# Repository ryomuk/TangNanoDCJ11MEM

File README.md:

# TangNanoDCJ11MEM
Memory system and UART implemented on Tang Nano 20K for DEC DCJ11 PDP-11 Processor

This document is written mostly in Japanese. If necessary, please use a translation service such as DeepL (I recommend this) or Google.

- 本プロジェクトはTang Console 138Kを用いた続編[TangConsoleDCJ11MEM](https://github.com/ryomuk/TangConsoleDCJ11MEM)があります．
- このREADMEおよび[hdl.old](./hdl.old)フォルダ配下のREADMEに書かれている不安定である旨の記述は2024年に作成したrev1.1基板のものです．rev.2.2になってかなり安定しましたが，記録として残しておきます．

# 概要
- PDP-11の命令セットを持つCPU「DEC DCJ11」のメモリシステムとUARTをFPGA(TangNano20K)上に実装する試みです．信号のインターフェース部分に[tangNano-5V](https://github.com/ryomuk/tangnano-5V)を使用しています．(rev.3.1基板では不要)
- FPGAに実装するのはメモリやUARTなどの周辺回路部分だけで，CPU自体は本物を使用します．ソフトウェアやFPGAによるシミュレータやエミュレータではなく，本物のCPUを動かします．
- "TangNanoDCJ11"だとTangNano上にDCJ11を実装したみたいな名前になってしまうので，"MEM"を付けて"TangNanoDCJ11MEM"という名前になっています．
- まずベアメタルで動かしたところ安定して動きました．
- 次に，PC-11(Paper-Tape Reader/Punch)エミュレータでPaper-Tape BASICをロードして実行することができました．
- さらに，UNIX first edition (UNIX V1)を動かすために，ディスク(RF11, RK11)や外部演算装置(KE11)のエミュレータを実装したところ，それなりに動くようになりました．

# 最近の話題
- 2025/09/03: 本プロジェクトの続編[TangConsoleDCJ11MEM](https://github.com/ryomuk/TangConsoleDCJ11MEM)を公開
- 2025/09/05: rev2.2基板公開
- 2025/09/22: レベル変換ICを搭載した基板rev3.1を公開
- 2025/09/29: RT-11 v4用のHDLを公開
- 最新版は下記の通り
  - レベル変換外付け版([rev2.2](pcb/rev2.2))．(別途[TangNano5V](https://github.com/ryomuk/tangnano-5V)が必要です．)
  - レベル変換搭載版([rev3.1](pcb/rev3.1))
  - 上記のどちらもHDLコードは共通です．
    - [UNIX用のHDLコード](./hdl/unix)(unix-v1, unix-v6 共通)
    - [tapebasic用のHDLコード](./hdl/tapebasic)
    - [RT11v4用のHDLコード](./hdl/rt11v4)

# 主なファイル一覧
```
.
├── diskimage : SDメモリ用データ
│   ├── Caldera-license.pdf : UNIXのライセンス条項
│   ├── sd-unix-v1.dsk      : unix v1用disk image
│   └── sd-unix-v6.dsk      : unix v6用disk image
├── hdl              : rev2.2, rev3.1基板用HDLコード
│   ├── rt11v4
│   ├── tapebasic
│   └── unix
├── hdl.old          : rev1.1基板用HDLコード
│   ├── baremetal
│   ├── tapebasic
│   ├── unix-v1
│   └── unix-v6
├── pcb
│   ├── rev1.1      : rev1.1基板
│   ├── rev2.2      : rev2.2基板
│   └── rev3.1      : rev3.1基板
└── README.md        : このファイル
```
- diskimageフォルダ内にあるSDメモリ用のイメージファイルはUNIXのオリジナルソースからの派生物なので，ライセンス条件は Caldera-license.pdf (昔のBSD?)に従います．
- その他の部分についてはMITライセンスです．

## Gowin FPGA Designerの設定について
- implフォルダをgitから除外したら設定ファイルも除外されてしまったのでコンパイル時にエラーが出るかもしれません．Configuration->Dual-Purpose Pin で"Use SSPI as regular IO"をチェックし下さい．

# 基板のバージョンについて
- [TangConsole138Kを用いたプロジェクト](https://github.com/ryomuk/TangConsoleDCJ11MEM)を開始した際に，CLK2に同期させるとかなり安定するという知見が得られたので，アップデートするついでに各種パッチを反映させた基板(rev2.2)を作成しました．
- ついでに，レベル変換を搭載した基板(rev3.1)も作成しました．
- それぞれの基板は下記のような関係にあります．
```
rev1.1
↓ unix v1, v6用パターンカット，ジャンパ, HALTのダイオード追加, CLK2同期化
rev2.2
↓ レベル変換(TangNano5V相当)を基板上に搭載(CPUの入力信号(FPGA→CPU)については省略)
rev3.1
```
- rev1.1基板に「unix-v1, v6用のパターンカット，ジャンパ線」，「CLK2とGPIO_RXを33Ωで接続」，「HALTのダイオード」を追加することでrev2.2基板と同じ回路になり，rev2.2基板用のHDLコードで動作します．
- rev3.1基板はrev2.2基板にレベル変換を搭載しただけなので同じHDLコードが動きます．
- rev1.1基板用のHDLコードはrev2.2, rev3.1基板では動きません．

# ハードウェア
## FPGAに実装した機能
- Initialization Sequence時のPower-Up Configuration Register設定
- メモリ 32K×16bit
- UART．TangNanoのUSB経由およびGPIO経由の2系統．シリアルの設定は基本的には115200bps,8N1Nにしています．(UNIX V6だと7N1Nにしないと文字化けする現象あり．)
- BS0, BS1は見ていません．TangNano20Kではピンが足りなかったのと，DAL[15:0]とAIO[3:0]を見ればとりあえず十分だったので．
- DAL[21:16]も見ていません．
- PC-11(Paper-Tape Reader/Punch)エミュレータを実装しました．(Paper tape BASICを実行する用で，UNIXでは動きません．)
- ディスクドライブ(RF11, RK11)，外部演算装置(KE11-A)，クロック(KW11-L)等，UNIX V1の動作に必要な装置のエミュレータを実装しました．

## rev3.1基板 (PCB rev3.1)
- レベル変換ICを基板上に実装しました．これによりTang Nano 20KをTangNano5Vを使わずに直接搭載できます．
- ピンアサインはrev2.2基板と同じなので，FPGA用のコードはrev2.2用のものを使用します．
- WS2812のアレイを接続するための端子を用意しました．
- レベル変換ICのOE_nをdisableにしてCPUとTangNanoを切り離すためのジャンパ端子を用意しました．(初めて搭載するときなど，FPGAに別の回路が書かれているようなとき用．)

#### BOM (PCB rev3.1)
|Reference          |Qty| Value          |Size |Memo |
|-------------------|---|----------------|-----|-----|
|C1,C2|2|68pF|||
|C3,C4, C5, C6|4|0.1uF|||
|C7,C8|2|0.33uF|||
|C9    |1|47uF|||
|D1    |1|1N4148|||
|J1    |1|IC socket |40pin DIP 800mil|TangNano20K用．幅800milなので1x20のpin socketを2列実装．|
|J2,J3|2  |pin header or socket|1x30|任意．テストや観測，実験用．|
|J4                 |1  |pin header      |1x02|任意．OE_nをdisableにする用|
|J5                 |1  |pin socket      |1x04 L字|WS2812アレイ用|
|J6                 |1  |pin header      |1x06 L字|UART用|
|LED1    |1||||
|R1 |1|1M|||
|R2 |1|33|||
|R3,R4,R5,R6,R7,R8,R9,R10,R11,R12,R13,R14,R15|13|10k|
|R16|1|100k  || 値はLEDに合わせて任意．|
|SW1,SW2  |2  |tactile SW      |6mmxH4.3mm|例: https://akizukidenshi.com/catalog/g/g103647/ |
|U1                 |1  |DCJ11           |60pin DIP 1300mil| 1x30 の丸ピンソケット2列|
|U2,U3,U4,U5  |4  |SN74CB3T3245DWR(又は DW) | SOIC-20| パッケージサイズに注意|

|Y1                 |1  |18MHz           |HC49|例: https://mou.sr/3WcWExh , 周波数を変えられるようにソケットの使用をお勧めします．|

- SN74CB3T3245はパッケージサイズに注意．SOIC-20はDWかDWRです．PWやPWRではありません．
- R2は"33k"ではなく"33"です．ダンピング抵抗なので．
- R12，最近のLEDは明るいので100kぐらいでちょうど良かったりします．使うLEDに応じて適切な値を選んで下さい．

## rev2.2基板 (PCB rev2.2)
- rev1.1基板でunixを動かすために必要だったパターンカットとジャンパ配線を反映させました．
- CLK2をGPIO_RXだったピンに入力して，回路をCPUのクロックと同期させました．
- 上記に伴い，基板のUART端子はデバッグログ用のTXだけになりました．
- 電源供給をTangNanoからだけにしてDCジャックを廃止しました．
- HALTスイッチのところの抵抗をダイオードに変更しました．
- unix(v1, v6)を動作させるためのプロジェクトは[hdl/unix](hdl/unix/)を使用して下さい．
- SDメモリ用のイメージファイルは[./diskimage](./diskimage)にあるものがそのまま使えます．

#### BOM (PCB rev2.2)
|Reference          |Qty| Value          |Size |Memo |
|-------------------|---|----------------|-----|-----|
|C1, C2|2|68pF|||
|C3, C4|2|0.33uF|||
|C5    |1|47uF|||
|D1    |1|1N4148|||
|J1    |1|IC socket |40pin DIP 600mil|TangNano5V用．1x20のpin socket 2列でも可．|
|J2,J3 |2|pin header or socket|1x20|任意．テストや観測，実験用．|
|J4,J5 |2  |pin header or socket|1x30|任意．テストや観測，実験用．|
|J6                 |1  |pin header      |1x06 L字|UART用|
|LED1    |1||||
|R1 |1|1M|||
|R2 |1|33|||
|R3,R4,R5,R6,R7,R8,R9,R10,R11,R12,R13,R14|12|10k|
|R15|1|100k  || 値はLEDに合わせて任意．|
|SW1,SW2  |2  |tactile SW      |6mmxH4.3mm|例: https://akizukidenshi.com/catalog/g/g103647/ |
|U1                 |1  |DCJ11           |60pin DIP 1300mil| 1x30 の丸ピンソケット2列|
|Y1                 |1  |18MHz           |HC49|例: https://mou.sr/3WcWExh , 周波数を変えられるようにソケットの使用をお勧めします．|

## rev1.1基板 (PCB rev1.1)
- rev1.0はいくつか修正箇所があったので修正しました．
- CPUが白いので基板も白くしてみました．
- CPUおよびTangNanoの電源をどこから供給するかを2箇所のジャンパで切り替えられるようにしました．詳細は回路図と基板上のシルクを見て下さい．
- プルダウン抵抗(R2〜R6)を100kから10kに変更しました．(rev1.1a)
- UNIXを動かすにはJP1のパターンのカット，数本のジャンパ配線が必要です．詳細は[UNIX V1](hdl.old/unix-v1/)参照．

#### BOM (PCB rev1.1)
|Reference          |Qty| Value          |Size |Memo |
|-------------------|---|----------------|-----|-----|
|C1,C2              |2	|0.33uF	         ||DECのプロセッサボードで0.33uFを使っていたので．0.1uFでもいいかもしれない．|
|C3                 |1  |47uF            |||
|C4,C5              |2  |68pF            |||
|D1                 |1  |LED             || |
|J1                 |1  |DC Jack         ||例: https://akizukidenshi.com/catalog/g/g106568/ |
|J2                 |1  |pin header      |1x02|DC Jackからの5VをTangNanoに供給するとき用．(そのときはTangNanoのUSBは外すこと)．|
|J3                 |1  |pin header      |1x03|CPUへの5VをDC JackからにするかUSB(TangNano)からにするかの選択用．|
|J4                 |1  |IC socket       |40pin DIP 600mil|TangNano5V用．1x20のpin socket 2列でも可．|
|J5,J6              |2  |pin header or socket|1x20|任意．テストや観測，実験用．|
|J7                 |1  |pin header      |1x06 L字|UART用|
|J8,J9              |2  |pin header or socket|1x30|任意．テストや観測，実験用．|
|JP1                |   |                ||任意．sctl_nとcont_nを切断したときにpin headerを立てる用．実装する場合は先にパターンをカットして下さい．(unix-v1では切断して使います)|
|R1                 |1  |100k            || 値はLEDに合わせて任意．|
|R2～R6             |5 |10k            || プルダウン用．入力電流がmax10μAなので大きめでいいかと思ったら意外にノイズが大きいので100kから10kに変更しました．|
|R7～R16             |10 |100k            || プルアップ用．10k〜100kぐらいで任意．|
|R17                |1  |1M              |||
|SW1                |1  |toggle SW       ||例: https://akizukidenshi.com/catalog/g/g100300/ |
|SW2,SW3            |2  |tactile SW      |6mmxH4.3mm|例: https://akizukidenshi.com/catalog/g/g103647/ |
|U1                 |1  |DCJ11           |60pin DIP 1300mil| 1x30 の丸ピンソケット2列|
|Y1                 |1  |18MHz           |HC49|例: https://mou.sr/3WcWExh , 低速(2MHzで確認済み,もっと遅くても動きそう)でも動きます．周波数を変えられるようにソケットの使用をお勧めします．|

# [応用例(hdl.old/)](hdl.old/)
## [ベアメタル(hdl.old/baremetal)](hdl.old/baremetal/)
- クロス環境で作成したプログラムを実行します．
- HDLは小規模なので，いろいろ試すベースラインに最適です．

## [tape basic(hdl.old/tapebasic)](hdl.old/tapebasic/)
- 二次記憶をエミュレートするために手始めに作った習作です．
- PC11(tape reader/pucnch)エミュレータで，tape BASICを読み込んで起動します．
- SDメモリを使う練習用に作ったものなのでとりあえず動きます程度のものです．
- PDP11GUIに，console ODT経由でpaper tape softwareをロードする機能があるようなので，いろいろなpaper tape softwareを試すという目的であればベアメタルでPDP11GUIを使うことをお勧めします．

## [UNIX V1(hdl.old/unix-v1)](hdl.old/unix-v1/)
- SDメモリを使ったdiskエミュレータを作成し，UNIX V1を動かしてみました．
- 最初はかなり不安定でしたが，だいぶ安定して動くようになってきました．

## [UNIX V6(hdl.old/unix-v6)](hdl.old/unix-v6/)(実験用)
- unix-v1用をベースにUNIX V6に必要な機能を逐次追加中です．修正のたびにV1の動作確認をするのは面倒なのでV1用と分けることにしました．

# 動画
- [PDP-11 Paper-Tape BASIC running on DCJ-11 Processor](https://www.youtube.com/watch?v=F_eFMz5ysK8)

- [UNIX V1 on DEC DCJ-11 with TangNano 20K (under development)](https://www.youtube.com/watch?v=DT7xJWeF46Y)

- [UNIX V1 on DEC DCJ-11 with TangNano 20K](https://www.youtube.com/watch?v=G9AFgAaTexo)

# 旧版
## ブレッドボード版
- console ODT(Octal Debug Technique)の動作確認をするところから始めて，[豊四季タイニーBASIC](https://github.com/vintagechips/ttbasic_arduino)を軽微な修正で動かせるところまで確認しました．
- クロックは18MHzで動きました．遅い方は2MHzでも動きました．

## PCB版 rev1.0
最初に作った基板です．とりあえず動きました．

# 関連情報
## データシート等
### bitsavers
- [DCJ11 Microprocessor User's Guide](http://www.bitsavers.org/pdf/dec/pdp11/1173/EK-DCJ11-UG-PRE_J11ug_Oct83.pdf), DEC, EK-DCJ11-UG-PRE(Preliminary)
- [Index of /pdf/dec/pdp11/j11](http://bitsavers.trailing-edge.com/pdf/dec/pdp11/j11/)
- [Index of /pdf/dec/pdp11/1173](http://bitsavers.trailing-edge.com/pdf/dec/pdp11/1173/)

## 先行事例，先駆者たち
- [PDP-11/HACK](http://madrona.ca/e/pdp11hack/index.html), Brent Hilpert
- [My PDP-11 Projects](https://www.5volts.ch/pages/pdp11hack/), Peter Schranz
- [PDP11 on a breadboard A.K.A. J11 Hack](https://www.chronworks.com/J11/), Len Bayles
- [S100 Bus PDP-11 CPU Board](http://www.s100computers.com/My%20System%20Pages/PDP11%20Board/PDP11%20Board.htm), John Monahan

## 開発環境関連
- [PDP-11(エミュ）上でCで"Hello, World!"](https://qiita.com/hifistar/items/8eff4a73087f3a41e19f), hifistar
- [PDP-11のgccクロスコンパイル環境の構築メモ](https://qiita.com/hifistar/items/187fd7ad780c6aa26141), hifistar
- [SimH (History Simulator)](http://simh.trailing-edge.com/)
- [j-hoppe/PDP11GUI](https://github.com/j-hoppe/PDP11GUI)

## Paper Tape Software関連
- [Paper Tape Archive](https://www.vaxhaven.com/Paper_Tape_Archive)
- [DEC PDP-11 Paper Tape Images](https://www.pcjs.org/software/dec/pdp11/tapes/)
- [PDP-11 Paper Tape BASIC](https://avitech.com.au/?page_id=709)
- [Learning PDP-11](https://www.learningpdp11.com/) Paper Tape BASICとboot loaderについてとても詳しく解説されています

## UNIX関連
- [The Unix Heritage Society](https://www.tuhs.org/)
- [V1](https://www.tuhs.org/cgi-bin/utree.pl?file=V1)
- [UNIX First Edition](https://gunkies.org/wiki/UNIX_First_Edition)
- [jserv/unix-v1](https://github.com/jserv/unix-v1)

## 関連記事
- [きょうのかんぱぱ](https://kanpapa.com/today/)
TangNanoDCJ11MEMを使って私がやっていないようなことまでやっていたり，ここのREADMEより詳しく解説されてたりします．
  - [TangNanoDCJ11MEMでPDP-11のCPUを動かしてみました 製作編](https://kanpapa.com/today/2024/07/pdp-11-dcj11-cpu-1.html), 
  - [TangNanoDCJ11MEMでPDP-11のCPUを動かしてみました bare metal編](https://kanpapa.com/today/2024/07/tangnanodcj11mem-pdp-11-cpu-2-bare-metal.html)
  - [TangNanoDCJ11MEMとPDP11GUIでPDP-11 BASICを動かしてみました](https://kanpapa.com/today/2024/08/tangnanodcj11mem-pdp-11-cpu-3-pdp11basic.html)
  - [PDP-11 DCJ11 CPUでUNIX v6を動かしてみました](https://kanpapa.com/today/2024/08/tangnanodcj11mem-pdp-11-cpu-4-unix-v6.html)
  - [PDP-11 DCJ11 CPUでMINI-UNIXを動かしてみました](https://kanpapa.com/today/2024/08/tangnanodcj11mem-pdp-11-dcj11-cpu-mini-unix.html)

# 更新履歴
- 2024/04/25: 初版公開
- 2024/04/25: README修正(BOM追加)
- 2024/05/05: 基板rev1.1の写真追加．project更新．
- 2024/05/05: README.md修正(開発環境関連の情報を追加)
- 2024/05/05: samplesにasciiart を追加
- 2024/05/22: PC-11(紙テープリーダ/パンチャ)エミュレータを実装
- 2024/06/19: SDHCの初期化部分にバグがあったので修正
- 2024/06/21: tapebasicのtop.vにバグがあったので修正
- 2024/06/21: baremetalとtapebasicを別フォルダに分離．READMEも分離．
- 2024/06/24: unix-v1用の開発中HDLを公開(かなり不安定です)
- 2024/06/28: tapebasicのtapeimage.datの作成方法を修正
- 2024/06/28: tapebasicのtapeimage.datの作成方法を修正
- 2024/07/07: baremetal版修正(UART安定化, 20240707公開)
- 2024/07/12: unix-v1版修正(20240712.alpha公開)
- 2024/07/13: unix-v1版修正(20240713.alpha公開)．IRQのジャンパ変更．
- 2024/07/14: unix-v1版修正(20240714.alpha公開)．デバッグ用レジスタ変更．
- 2024/07/15: プルダウン抵抗(R2〜R6)を100kから10kに変更．100kで問題が起きていなければ変える必要は無いです．
- 2024/07/16: unix-v1版大規模修正(20240716.beta公開)．JP1(SCTL_nとCONT_nを接続してるパターンをカットして下さい．)
- 2024/07/19: unix-v1 20240719.beta 公開．これまでのバージョンと比較するとだいぶ安定しました．
- 2024/07/27: unix-v1 20240727.beta 公開．
- 2024/07/28: unix-v1 20240728.beta 公開．(UNIX V6実験用機能追加)
- 2024/07/29: V6実験用とV1用を分離しました．
  - unix-v1 20240729.beta 公開．
  - unix-v6 20240729.v6.beta 公開．
- 2025/09/04: rev2.0基板公開．
- 2025/09/05: rev2.2基板公開．
- 2025/09/06: README修正(HALTのジャンパ関連(main, unix-v1, unix-v6), rev3基板予告)
- 2025/09/15: 20250915.pcbrev2 公開．(LEDアレイ用の記述を追加)
- 2025/09/17: 20250917.pcbrev2 公開．(SDメモリ無しで動かすときの問題を修正)
- 2025/09/22: フォルダ構成変更．
  - rev3.1基板公開．
  - 20250922公開．
- 2025/09/29: RT11 v4用HDL公開．

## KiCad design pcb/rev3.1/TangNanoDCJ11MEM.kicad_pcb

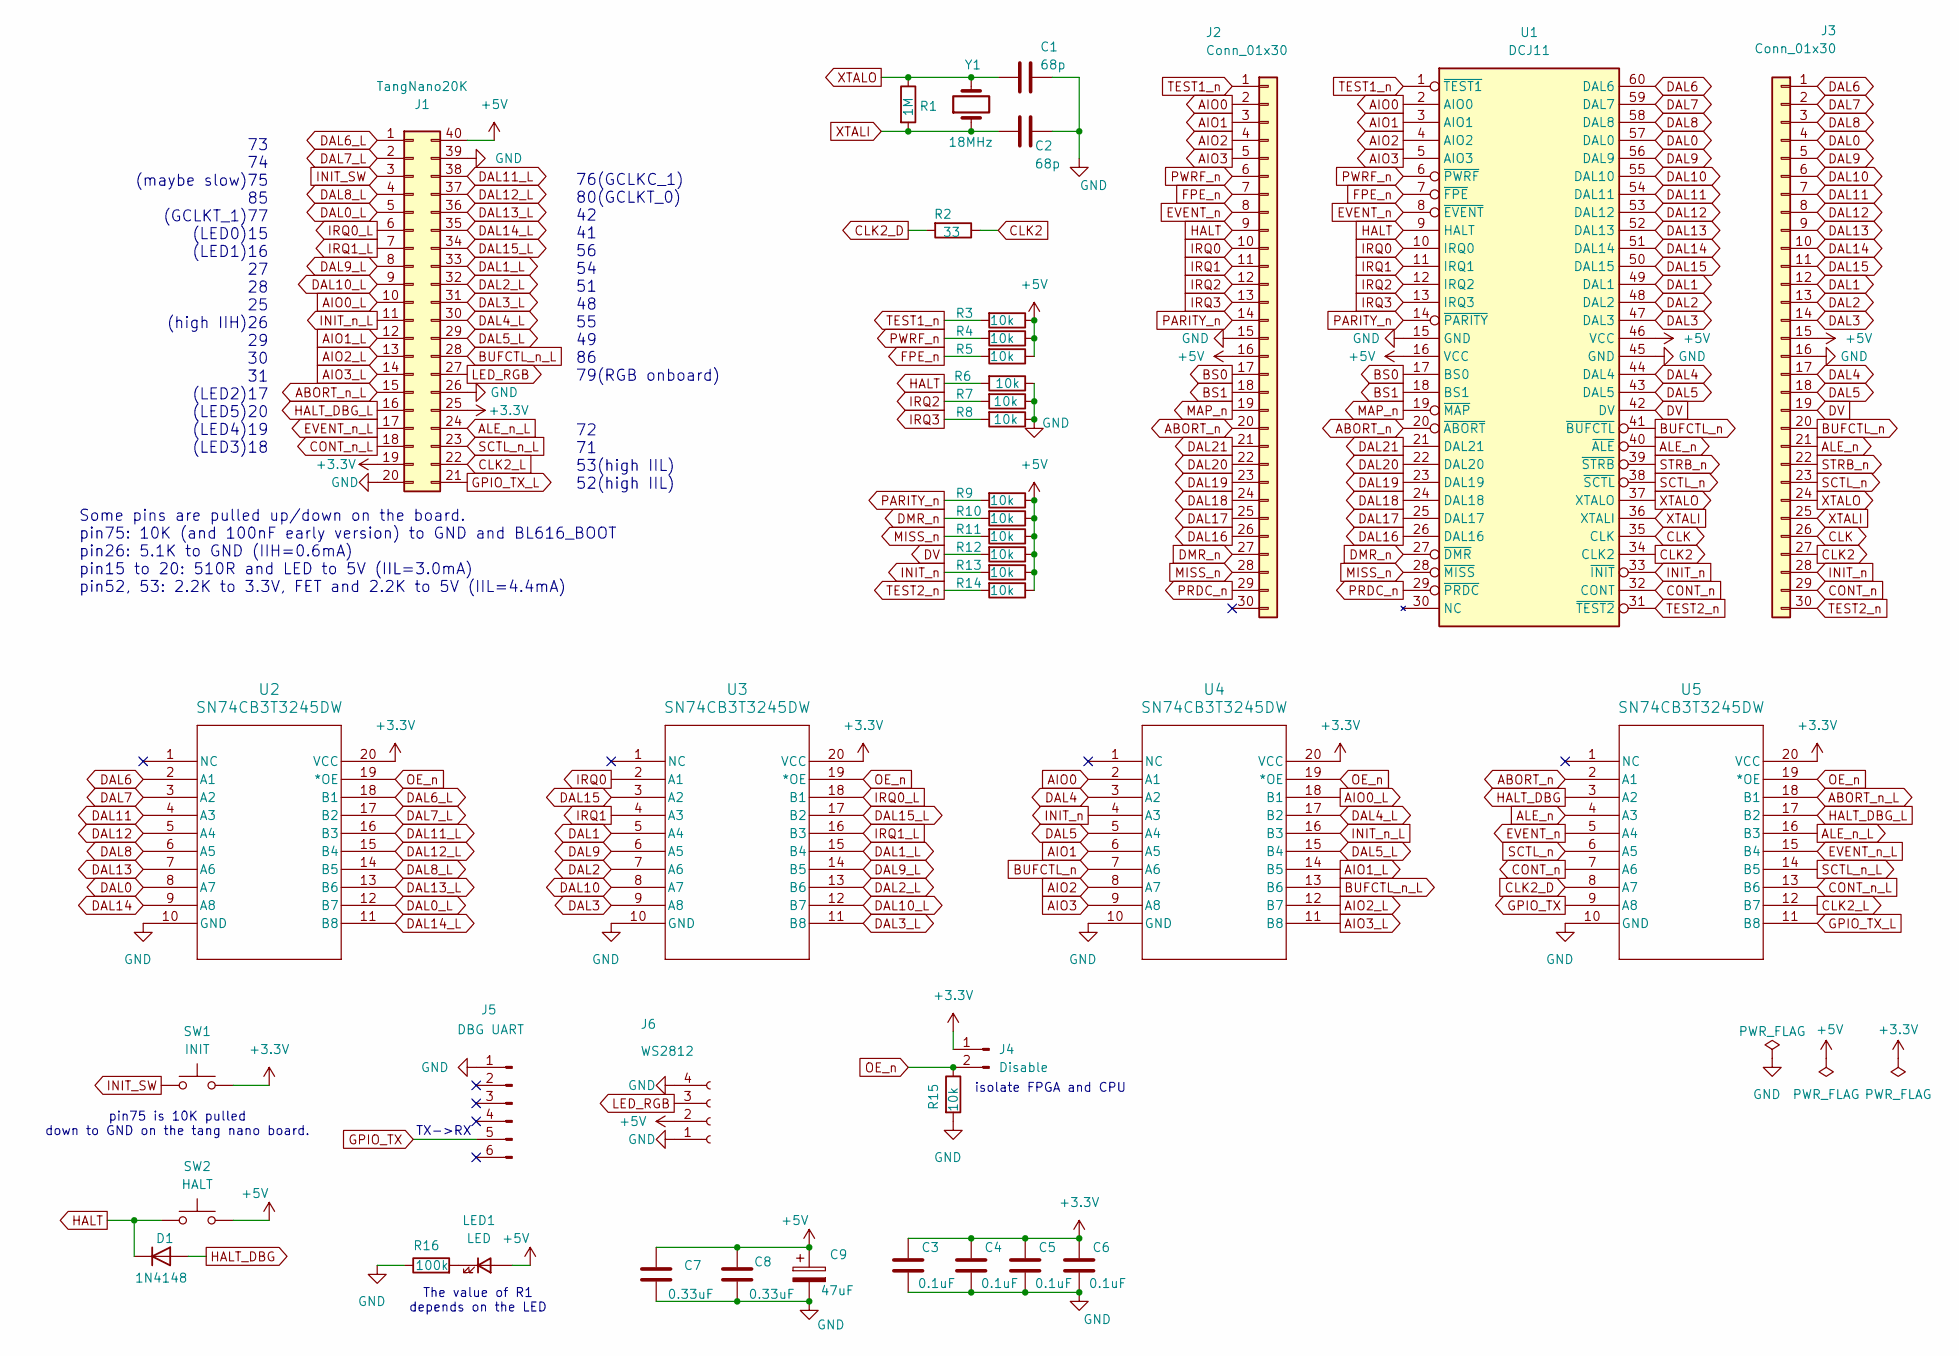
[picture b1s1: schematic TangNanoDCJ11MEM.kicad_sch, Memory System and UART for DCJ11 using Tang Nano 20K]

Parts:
C1, C2: 68p; C_Disc_D5.0mm_W2.5mm_P2.50mm
C3, C4, C5, C6: 0.1uF; C_Disc_D5.0mm_W2.5mm_P2.50mm
C7, C8: 0.33uF; C_Disc_D5.0mm_W2.5mm_P2.50mm
C9: 47uF; CP_Radial_D6.3mm_P2.50mm
D1: 1N4148; D_T-1_P5.08mm_Horizontal
J1: TangNano20K; DIP-40_W20.32mm800mil_Socket
J2, J3: Conn_01x30; PinSocket_1x30_P2.54mm_Vertical
J4: Disable; JumperedPinHeader_1x02_P2.54mm_Vertical
J5: DBG UART; PinHeader_1x06_P2.54mm_Horizontal
J6: WS2812; PinSocket_1x04_P2.54mm_Horizontal
LED1: LED; LED_D3.0mm
R1: 1M; R_Axial_DIN0207_L6.3mm_D2.5mm_P7.62mm_Horizontal
R2: 33; R_Axial_DIN0207_L6.3mm_D2.5mm_P7.62mm_Horizontal
R3, R4, R5, R6, R7, R8, R9, R10, R11, R12, R13, R14, R15: 10k; R_Axial_DIN0207_L6.3mm_D2.5mm_P7.62mm_Horizontal
R16: 100k; R_Axial_DIN0207_L6.3mm_D2.5mm_P7.62mm_Horizontal
SW1: INIT; SW_PUSH_6mm_H4.3mm
SW2: HALT; SW_PUSH_6mm_H4.3mm
U1: DCJ11; DIP-60_W33.02mm_LongPads
U2, U3, U4, U5: SN74CB3T3245DW; DW20
Y1: 18MHz; Crystal_HC49-U_Vertical

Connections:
+3.3V: C3.1, C4.1, C5.1, C6.1, J1.19, J1.25, J4.1, SW1.1, U2.20 (VCC), U3.20 (VCC), U4.20 (VCC), U5.20 (VCC)
+5V: C7.1, C8.1, C9.1, J1.40, J2.16, J3.15, J6.2, LED1.2 (A), R3.1, R4.1, R5.1, R9.1, R10.1, R11.1, R12.1, R13.1, R14.1, SW2.1, U1.16 (VCC), U1.46 (VCC)
ABORT_n: J2.20, U1.20 (~ABORT), U5.2 (A1)
ABORT_n_L: J1.15, U5.18 (B1)
AIO0: J2.2, U1.2 (AIO0), U4.2 (A1)
AIO0_L: J1.10, U4.18 (B1)
AIO1: J2.3, U1.3 (AIO1), U4.6 (A5)
AIO1_L: J1.12, U4.14 (B5)
AIO2: J2.4, U1.4 (AIO2), U4.8 (A7)
AIO2_L: J1.13, U4.12 (B7)
AIO3: J2.5, U1.5 (AIO3), U4.9 (A8)
AIO3_L: J1.14, U4.11 (B8)
ALE_n: J3.21, U1.40 (~ALE), U5.4 (A3)
ALE_n_L: J1.24, U5.16 (B3)
BS0: J2.17, U1.17 (BS0)
BS1: J2.18, U1.18 (BS1)
BUFCTL_n: J3.20, U1.41 (~BUFCTL), U4.7 (A6)
BUFCTL_n_L: J1.28, U4.13 (B6)
CLK: J3.26, U1.35 (CLK)
CLK2: J3.27, R2.1, U1.34 (CLK2)
CLK2_D: R2.2, U5.8 (A7)
CLK2_L: J1.22, U5.12 (B7)
CONT_n: J3.29, U1.32 (CONT), U5.7 (A6)
CONT_n_L: J1.18, U5.13 (B6)
DAL0: J3.4, U1.57 (DAL0), U2.8 (A7)
DAL0_L: J1.5, U2.12 (B7)
DAL1: J3.12, U1.49 (DAL1), U3.5 (A4)
DAL1_L: J1.33, U3.15 (B4)
DAL2: J3.13, U1.48 (DAL2), U3.7 (A6)
DAL2_L: J1.32, U3.13 (B6)
DAL3: J3.14, U1.47 (DAL3), U3.9 (A8)
DAL3_L: J1.31, U3.11 (B8)
DAL4: J3.17, U1.44 (DAL4), U4.3 (A2)
DAL4_L: J1.30, U4.17 (B2)
DAL5: J3.18, U1.43 (DAL5), U4.5 (A4)
DAL5_L: J1.29, U4.15 (B4)
DAL6: J3.1, U1.60 (DAL6), U2.2 (A1)
DAL6_L: J1.1, U2.18 (B1)
DAL7: J3.2, U1.59 (DAL7), U2.3 (A2)
DAL7_L: J1.2, U2.17 (B2)
DAL8: J3.3, U1.58 (DAL8), U2.6 (A5)
DAL8_L: J1.4, U2.14 (B5)
DAL9: J3.5, U1.56 (DAL9), U3.6 (A5)
DAL9_L: J1.8, U3.14 (B5)
DAL10: J3.6, U1.55 (DAL10), U3.8 (A7)
DAL10_L: J1.9, U3.12 (B7)
DAL11: J3.7, U1.54 (DAL11), U2.4 (A3)
DAL11_L: J1.38, U2.16 (B3)
DAL12: J3.8, U1.53 (DAL12), U2.5 (A4)
DAL12_L: J1.37, U2.15 (B4)
DAL13: J3.9, U1.52 (DAL13), U2.7 (A6)
DAL13_L: J1.36, U2.13 (B6)
DAL14: J3.10, U1.51 (DAL14), U2.9 (A8)
DAL14_L: J1.35, U2.11 (B8)
DAL15: J3.11, U1.50 (DAL15), U3.3 (A2)
DAL15_L: J1.34, U3.17 (B2)
DAL16: J2.26, U1.26 (DAL16)
DAL17: J2.25, U1.25 (DAL17)
DAL18: J2.24, U1.24 (DAL18)
DAL19: J2.23, U1.23 (DAL19)
DAL20: J2.22, U1.22 (DAL20)
DAL21: J2.21, U1.21 (DAL21)
DMR_n: J2.27, R10.2, U1.27 (~DMR)
DV: J3.19, R12.2, U1.42 (DV)
EVENT_n: J2.8, U1.8 (~EVENT), U5.5 (A4)
EVENT_n_L: J1.17, U5.15 (B4)
FPE_n: J2.7, R5.2, U1.7 (~FPE)
GND: C1.1, C2.1, C3.2, C4.2, C5.2, C6.2, C7.2, C8.2, C9.2, J1.20, J1.26, J1.39, J2.15, J3.16, J5.1, J6.1, J6.4, R6.1, R7.1, R8.1, R15.2, R16.1, U1.15 (GND), U1.45 (GND), U2.10 (GND), U3.10 (GND), U4.10 (GND), U5.10 (GND)
GPIO_TX: J5.5, U5.9 (A8)
GPIO_TX_L: J1.21, U5.11 (B8)
HALT: D1.1 (K), J2.9, R6.2, SW2.2, U1.9 (HALT)
HALT_DBG: D1.2 (A), U5.3 (A2)
HALT_DBG_L: J1.16, U5.17 (B2)
INIT_SW: J1.3, SW1.2
INIT_n: J3.28, R13.2, U1.33 (~INIT), U4.4 (A3)
INIT_n_L: J1.11, U4.16 (B3)
IRQ0: J2.10, U1.10 (IRQ0), U3.2 (A1)
IRQ0_L: J1.6, U3.18 (B1)
IRQ1: J2.11, U1.11 (IRQ1), U3.4 (A3)
IRQ1_L: J1.7, U3.16 (B3)
IRQ2: J2.12, R7.2, U1.12 (IRQ2)
IRQ3: J2.13, R8.2, U1.13 (IRQ3)
LED_RGB: J1.27, J6.3
MAP_n: J2.19, U1.19 (~MAP)
MISS_n: J2.28, R11.2, U1.28 (~MISS)
unnamed: LED1.1 (K), R16.2
OE_n: J4.2, R15.1, U2.19 (*OE), U3.19 (*OE), U4.19 (*OE), U5.19 (*OE)
PARITY_n: J2.14, R9.2, U1.14 (~PARITY)
PRDC_n: J2.29, U1.29 (~PRDC)
PWRF_n: J2.6, R4.2, U1.6 (~PWRF)
SCTL_n: J3.23, U1.38 (~SCTL), U5.6 (A5)
SCTL_n_L: J1.23, U5.14 (B5)
STRB_n: J3.22, U1.39 (~STRB)
TEST1_n: J2.1, R3.2, U1.1 (~TEST1)
TEST2_n: J3.30, R14.2, U1.31 (~TEST2)
XTALI: C2.2, J3.25, R1.2, U1.36 (XTALI), Y1.1
XTALO: C1.2, J3.24, R1.1, U1.37 (XTALO), Y1.2

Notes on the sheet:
isolate FPGA and CPU
72 71 53(high IIL) 52(high IIL)
73 74 (maybe slow)75 85 (GCLKT_1)77 (LED0)15 (LED1)16 27 28 25 (high IIH)26 29 30 31 (LED2)17 (LED5)20 (LED4)19 (LED3)18
76(GCLKC_1) 80(GCLKT_0) 42 41 56 54 51 48 55 49 86 79(RGB onboard)
Some pins are pulled up/down on the board. pin75: 10K (and 100nF early version) to GND and BL616_BOOT pin26: 5.1K to GND (IIH=0.6mA) pin15 to 20: 510R and LED to 5V (IIL=3.0mA) pin52, 53: 2.2K to 3.3V, FET and 2.2K to 5V (IIL=4.4mA)
The value of R1 depends on the LED
TX->RX
pin75 is 10K pulled down to GND on the tang nano board.

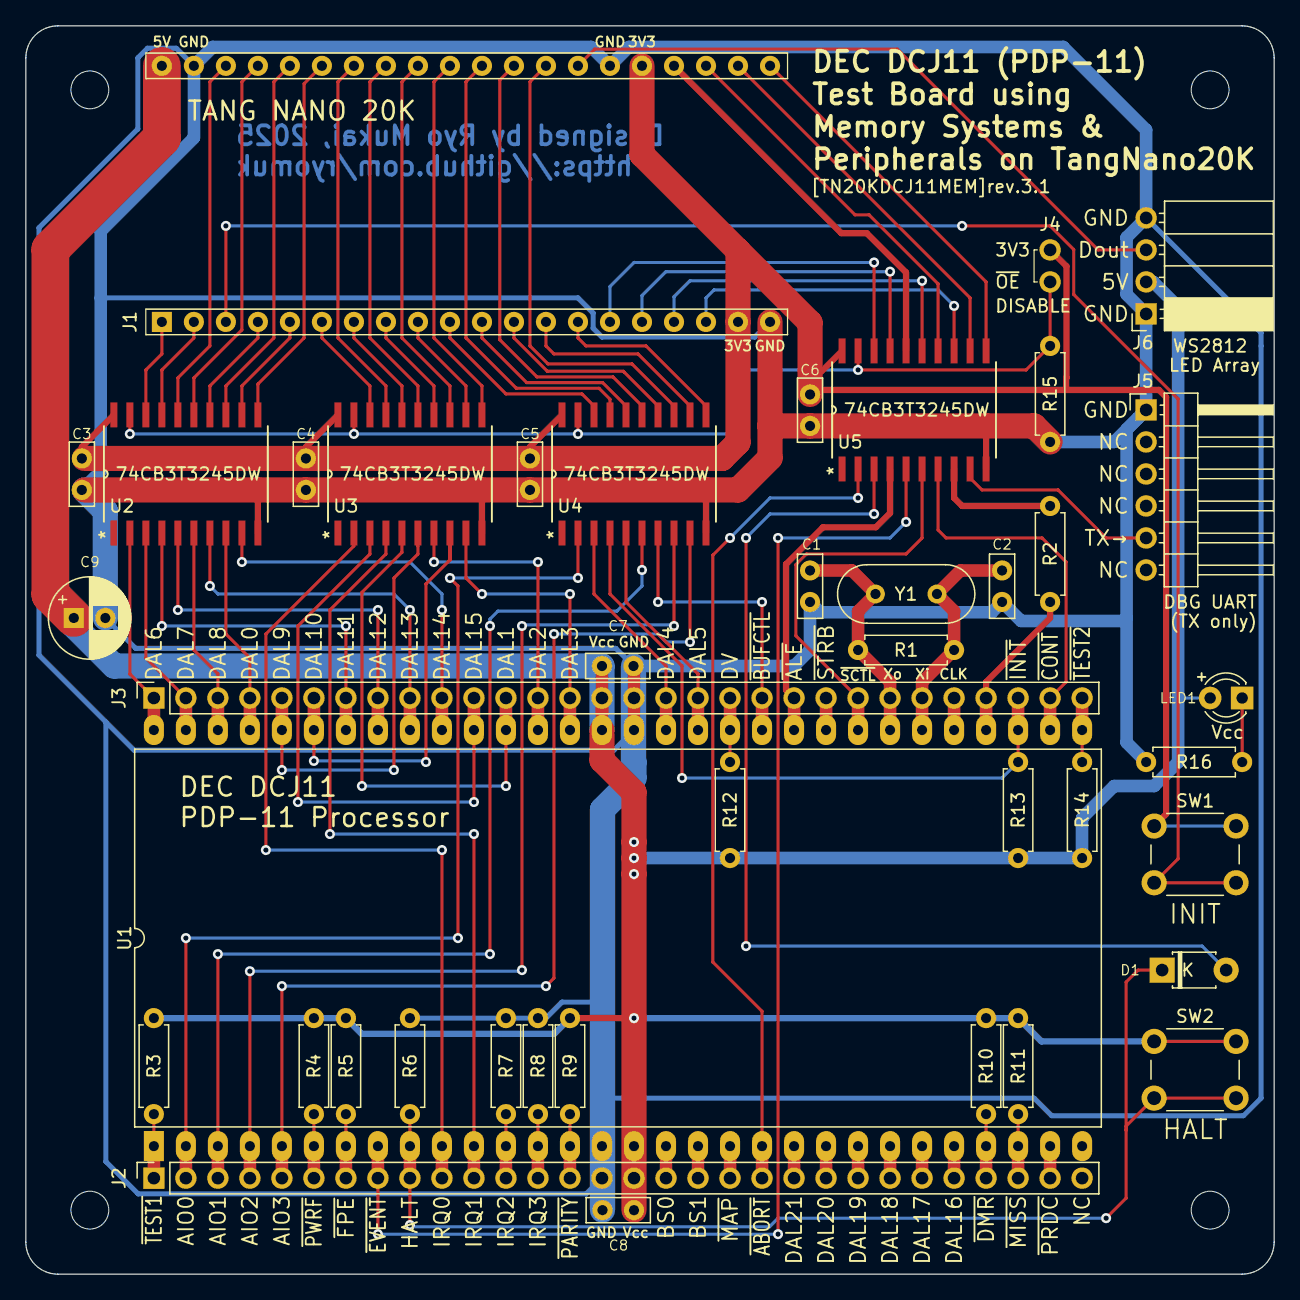
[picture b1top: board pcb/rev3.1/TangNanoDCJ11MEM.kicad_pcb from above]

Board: 2 copper layers, 99.1 x 99.1 mm, 41 parts (0 on the bottom side), 97 nets.

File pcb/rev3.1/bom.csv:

"Reference","Value","Datasheet","Footprint","Qty","DNP"
"C1,C2","68p","~","000_MyFootprint:C_Disc_D5.0mm_W2.5mm_P2.50mm","2",""
"C3,C4,C5,C6","0.1uF","~","000_MyFootprint:C_Disc_D5.0mm_W2.5mm_P2.50mm","4",""
"C7,C8","0.33uF","~","000_MyFootprint:C_Disc_D5.0mm_W2.5mm_P2.50mm","2",""
"C9","47uF","~","000_MyFootprint:CP_Radial_D6.3mm_P2.50mm","1",""
"D1","1N4148","","000_MyFootprint:D_T-1_P5.08mm_Horizontal","1",""
"J1","TangNano20K","~","000_MyFootprint:DIP-40_W20.32mm800mil_Socket","1",""
"J2,J3","Conn_01x30","~","000_MyFootprint:PinSocket_1x30_P2.54mm_Vertical","2",""
"J4","Disable","~","000_MyFootprint:JumperedPinHeader_1x02_P2.54mm_Vertical","1",""
"J5","DBG UART","~","000_MyFootprint:PinHeader_1x06_P2.54mm_Horizontal","1",""
"J6","WS2812","~","000_MyFootprint:PinSocket_1x04_P2.54mm_Horizontal","1",""
"LED1","LED","~","000_MyFootprint:LED_D3.0mm","1",""
"R1","1M","~","000_MyFootprint:R_Axial_DIN0207_L6.3mm_D2.5mm_P7.62mm_Horizontal","1",""
"R2","33","~","000_MyFootprint:R_Axial_DIN0207_L6.3mm_D2.5mm_P7.62mm_Horizontal","1",""
"R3,R4,R5,R6,R7,R8,R9,R10,R11,R12,R13,R14,R15","10k","~","000_MyFootprint:R_Axial_DIN0207_L6.3mm_D2.5mm_P7.62mm_Horizontal","13",""
"R16","100k","~","000_MyFootprint:R_Axial_DIN0207_L6.3mm_D2.5mm_P7.62mm_Horizontal","1",""
"SW1","INIT","~","000_MyFootprint:SW_PUSH_6mm_H4.3mm","1",""
"SW2","HALT","~","000_MyFootprint:SW_PUSH_6mm_H4.3mm","1",""
"U1","DCJ11","","000_MyFootprint:DIP-60_W33.02mm_LongPads","1",""
"U2,U3,U4,U5","SN74CB3T3245DW","SN74CB3T3245DW","000_MyFootprint:DW20","4",""
"Y1","18MHz","~","000_MyFootprint:Crystal_HC49-U_Vertical","1",""

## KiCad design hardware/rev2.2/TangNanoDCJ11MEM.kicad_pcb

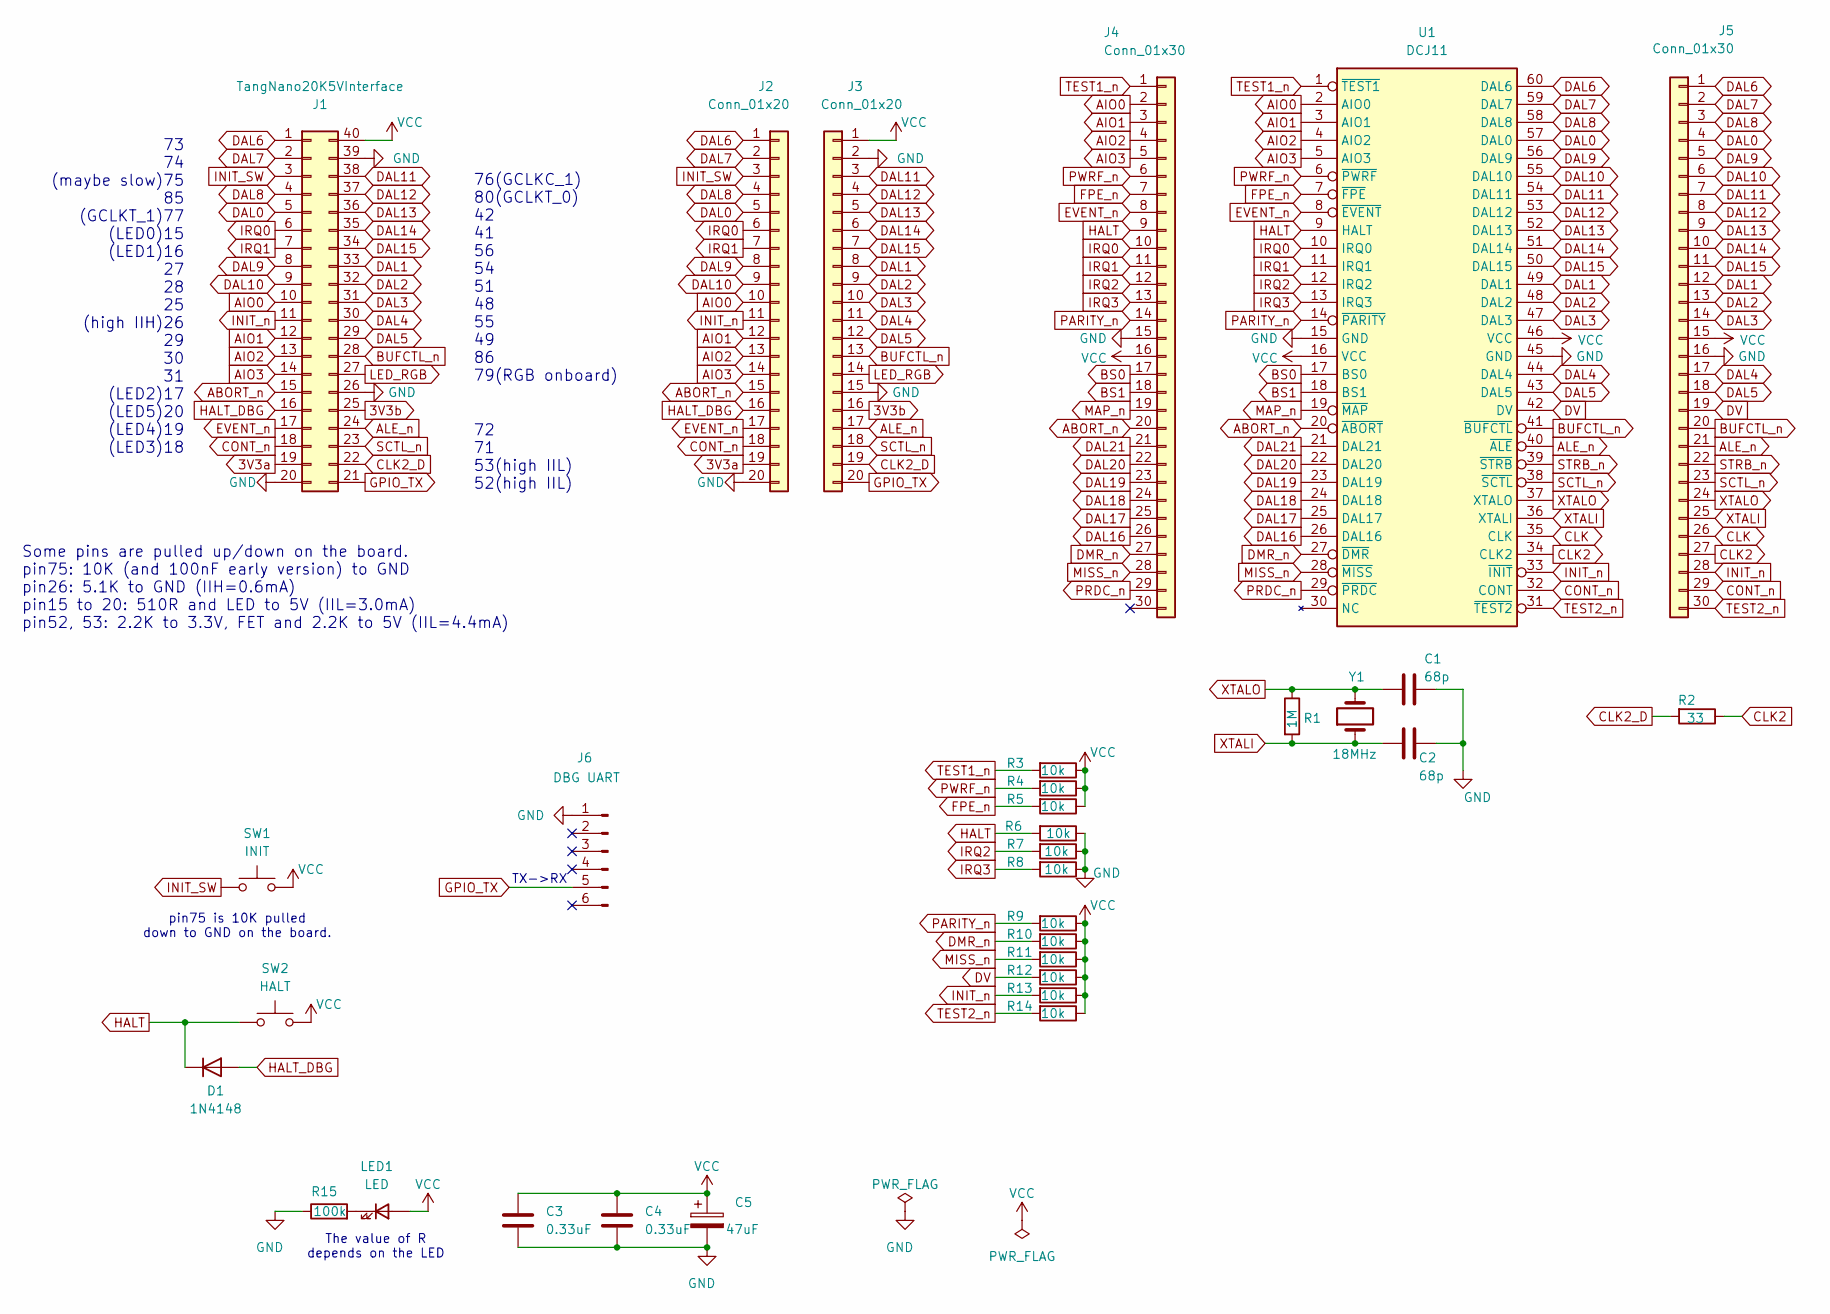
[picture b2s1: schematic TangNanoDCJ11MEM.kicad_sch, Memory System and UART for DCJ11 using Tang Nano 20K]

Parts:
C1, C2: 68p; C_Disc_D5.0mm_W2.5mm_P2.50mm
C3, C4: 0.33uF; C_Disc_D5.0mm_W2.5mm_P2.50mm
C5: 47uF; CP_Radial_D6.3mm_P2.50mm
D1: 1N4148; D_DO-35_SOD27_P7.62mm_Horizontal
J1: TangNano20K5VInterface; DIP-40_W15.24mm_Socket
J2, J3: Conn_01x20; PinSocket_1x20_P2.54mm_Vertical
J4, J5: Conn_01x30; PinSocket_1x30_P2.54mm_Vertical
J6: DBG UART; PinHeader_1x06_P2.54mm_Horizontal
LED1: LED; LED_D3.0mm
R1: 1M; R_Axial_DIN0207_L6.3mm_D2.5mm_P7.62mm_Horizontal
R2: 33; R_Axial_DIN0207_L6.3mm_D2.5mm_P7.62mm_Horizontal
R3, R4, R5, R6, R7, R8, R9, R10, R11, R12, R13, R14: 10k; R_Axial_DIN0207_L6.3mm_D2.5mm_P7.62mm_Horizontal
R15: 100k; R_Axial_DIN0207_L6.3mm_D2.5mm_P7.62mm_Horizontal
SW1: INIT; SW_PUSH_6mm_H4.3mm
SW2: HALT; SW_PUSH_6mm_H4.3mm
U1: DCJ11; DIP-60_W33.02mm_LongPads
Y1: 18MHz; Crystal_HC49-U_Vertical

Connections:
3V3a: J1.19, J2.19
3V3b: J1.25, J3.16
ABORT_n: J1.15, J2.15, J4.20, U1.20 (~ABORT)
AIO0: J1.10, J2.10, J4.2, U1.2 (AIO0)
AIO1: J1.12, J2.12, J4.3, U1.3 (AIO1)
AIO2: J1.13, J2.13, J4.4, U1.4 (AIO2)
AIO3: J1.14, J2.14, J4.5, U1.5 (AIO3)
ALE_n: J1.24, J3.17, J5.21, U1.40 (~ALE)
BS0: J4.17, U1.17 (BS0)
BS1: J4.18, U1.18 (BS1)
BUFCTL_n: J1.28, J3.13, J5.20, U1.41 (~BUFCTL)
CLK: J5.26, U1.35 (CLK)
CLK2: J5.27, R2.1, U1.34 (CLK2)
CLK2_D: J1.22, J3.19, R2.2
CONT_n: J1.18, J2.18, J5.29, U1.32 (CONT)
DAL0: J1.5, J2.5, J5.4, U1.57 (DAL0)
DAL1: J1.33, J3.8, J5.12, U1.49 (DAL1)
DAL2: J1.32, J3.9, J5.13, U1.48 (DAL2)
DAL3: J1.31, J3.10, J5.14, U1.47 (DAL3)
DAL4: J1.30, J3.11, J5.17, U1.44 (DAL4)
DAL5: J1.29, J3.12, J5.18, U1.43 (DAL5)
DAL6: J1.1, J2.1, J5.1, U1.60 (DAL6)
DAL7: J1.2, J2.2, J5.2, U1.59 (DAL7)
DAL8: J1.4, J2.4, J5.3, U1.58 (DAL8)
DAL9: J1.8, J2.8, J5.5, U1.56 (DAL9)
DAL10: J1.9, J2.9, J5.6, U1.55 (DAL10)
DAL11: J1.38, J3.3, J5.7, U1.54 (DAL11)
DAL12: J1.37, J3.4, J5.8, U1.53 (DAL12)
DAL13: J1.36, J3.5, J5.9, U1.52 (DAL13)
DAL14: J1.35, J3.6, J5.10, U1.51 (DAL14)
DAL15: J1.34, J3.7, J5.11, U1.50 (DAL15)
DAL16: J4.26, U1.26 (DAL16)
DAL17: J4.25, U1.25 (DAL17)
DAL18: J4.24, U1.24 (DAL18)
DAL19: J4.23, U1.23 (DAL19)
DAL20: J4.22, U1.22 (DAL20)
DAL21: J4.21, U1.21 (DAL21)
DMR_n: J4.27, R10.2, U1.27 (~DMR)
DV: J5.19, R12.2, U1.42 (DV)
EVENT_n: J1.17, J2.17, J4.8, U1.8 (~EVENT)
FPE_n: J4.7, R5.2, U1.7 (~FPE)
GND: C1.1, C2.1, C3.2, C4.2, C5.2, J1.20, J1.26, J1.39, J2.20, J3.2, J3.15, J4.15, J5.16, J6.1, R6.1, R7.1, R8.1, R15.1, U1.15 (GND), U1.45 (GND)
GPIO_TX: J1.21, J3.20, J6.5
HALT: D1.1 (K), J4.9, R6.2, SW2.2, U1.9 (HALT)
HALT_DBG: D1.2 (A), J1.16, J2.16
INIT_SW: J1.3, J2.3, SW1.2
INIT_n: J1.11, J2.11, J5.28, R13.2, U1.33 (~INIT)
IRQ0: J1.6, J2.6, J4.10, U1.10 (IRQ0)
IRQ1: J1.7, J2.7, J4.11, U1.11 (IRQ1)
IRQ2: J4.12, R7.2, U1.12 (IRQ2)
IRQ3: J4.13, R8.2, U1.13 (IRQ3)
LED_RGB: J1.27, J3.14
MAP_n: J4.19, U1.19 (~MAP)
MISS_n: J4.28, R11.2, U1.28 (~MISS)
unnamed: LED1.1 (K), R15.2
PARITY_n: J4.14, R9.2, U1.14 (~PARITY)
PRDC_n: J4.29, U1.29 (~PRDC)
PWRF_n: J4.6, R4.2, U1.6 (~PWRF)
SCTL_n: J1.23, J3.18, J5.23, U1.38 (~SCTL)
STRB_n: J5.22, U1.39 (~STRB)
TEST1_n: J4.1, R3.2, U1.1 (~TEST1)
TEST2_n: J5.30, R14.2, U1.31 (~TEST2)
VCC: C3.1, C4.1, C5.1, J1.40, J3.1, J4.16, J5.15, LED1.2 (A), R3.1, R4.1, R5.1, R9.1, R10.1, R11.1, R12.1, R13.1, R14.1, SW1.1, SW2.1, U1.16 (VCC), U1.46 (VCC)
XTALI: C2.2, J5.25, R1.2, U1.36 (XTALI), Y1.1
XTALO: C1.2, J5.24, R1.1, U1.37 (XTALO), Y1.2

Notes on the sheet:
72 71 53(high IIL) 52(high IIL)
73 74 (maybe slow)75 85 (GCLKT_1)77 (LED0)15 (LED1)16 27 28 25 (high IIH)26 29 30 31 (LED2)17 (LED5)20 (LED4)19 (LED3)18
76(GCLKC_1) 80(GCLKT_0) 42 41 56 54 51 48 55 49 86 79(RGB onboard)
Some pins are pulled up/down on the board. pin75: 10K (and 100nF early version) to GND pin26: 5.1K to GND (IIH=0.6mA) pin15 to 20: 510R and LED to 5V (IIL=3.0mA) pin52, 53: 2.2K to 3.3V, FET and 2.2K to 5V (IIL=4.4mA)
The value of R depends on the LED
TX->RX
pin75 is 10K pulled down to GND on the board.

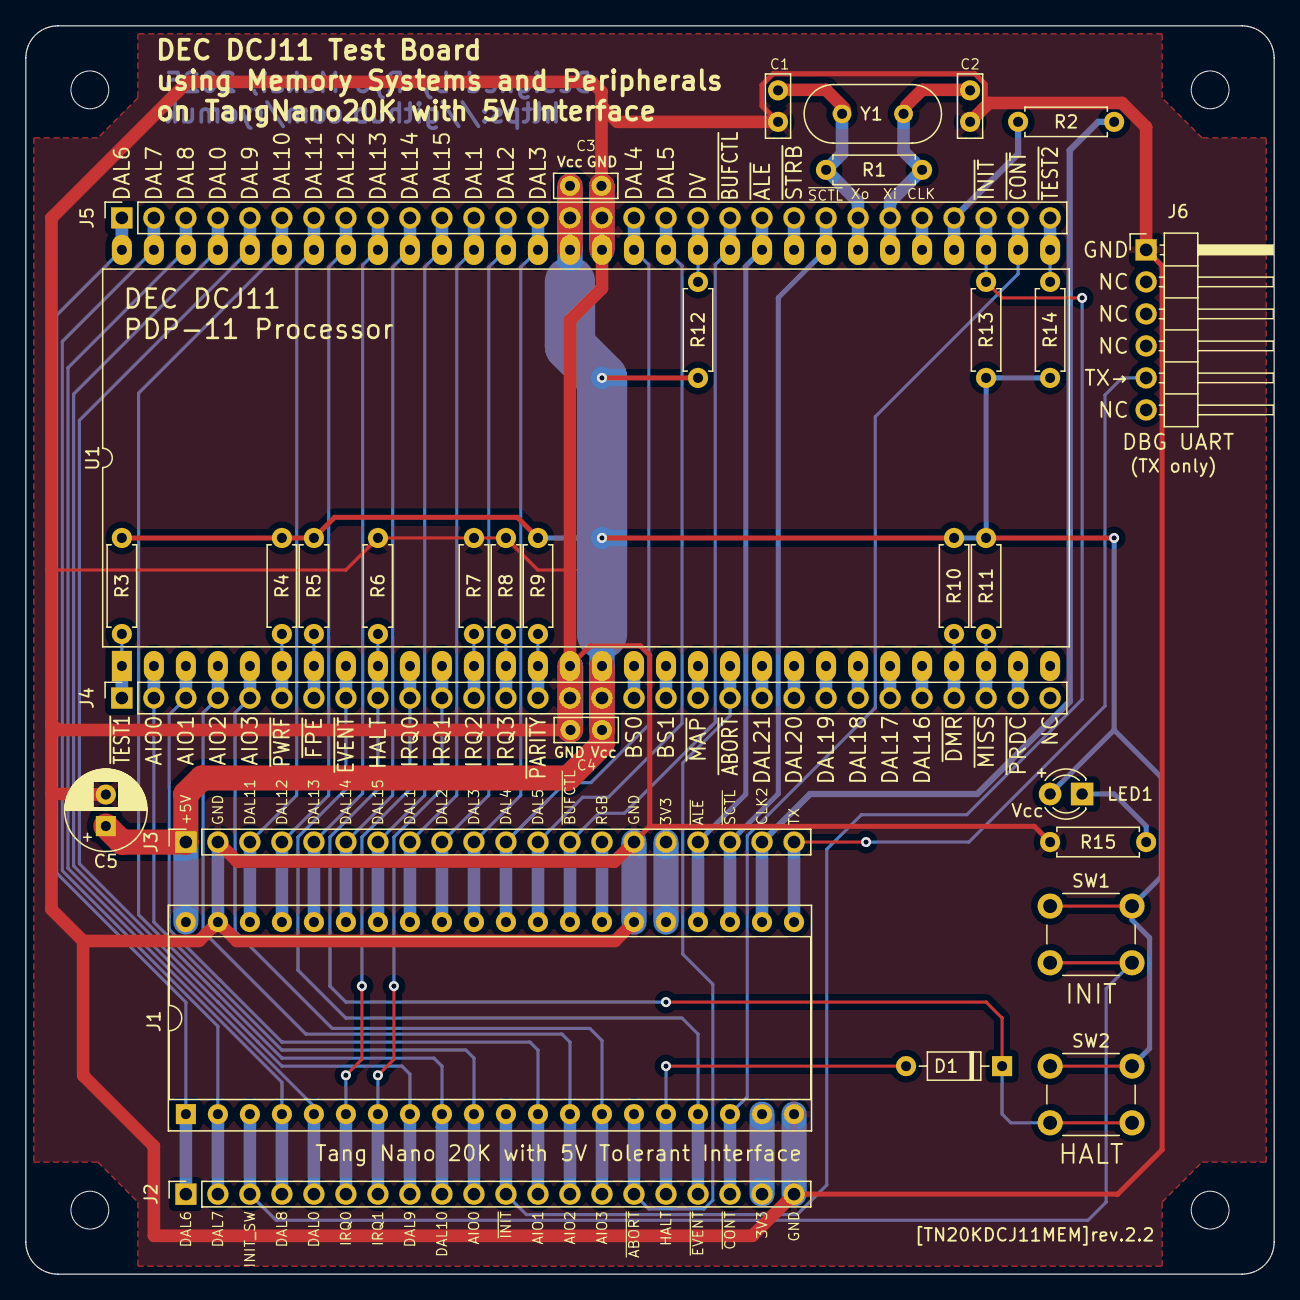
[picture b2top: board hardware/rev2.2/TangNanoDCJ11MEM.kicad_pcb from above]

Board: 2 copper layers, 99.1 x 99.1 mm, 32 parts (0 on the bottom side), 65 nets.
